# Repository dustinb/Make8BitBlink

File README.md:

# Make 8 Bit Blink

This is a program loader for [Ben Eater's 8 bit computer](https://eater.net/8bit/).  This is a work in progress.

# BOM

| Item                   | Link                   |
|------------------------|------------------------|
| ESP32                  | https://a.co/d/88cG9Z5 |
| 74HC595 Shift Register | https://a.co/d/fSzBLRR |
| PN2222 Transistors     | https://a.co/d/9t9HXHG |
| 40pin Socket Headers   | https://a.co/d/aSeVX48 |
| 22awg Hookup Wire      | https://a.co/d/aD9MhwA |

# Overview

The ESP32 polls the api (`/run` endpoint) for programs periodically.  If a program is in a queue the loader hatls the computer and loads the program.

# API

The api can by running `docker compose up` in the api directory.

Programs are queued in the order they are received.  A program can be queued by POSTing to the `/program` endpoint with the following JSON structure.

```json
{
    "clockSpeed": 100,
    "time": 20,
    "name": "42",
    "memory": [
        {
            "address": 14,
            "value": 28
        },
        {
            "address": 15,
            "value": 14
        }
    ],
    "instructions": [
        {
            "name": "LDA",
            "argument": 14
        },
        {
            "name": "ADD",
            "argument": 15
        },
        {
            "name": "OUT",
            "argument": 0
        },
        {
            "name": "HLT",
            "argument": 0
        }
    ]
}
```

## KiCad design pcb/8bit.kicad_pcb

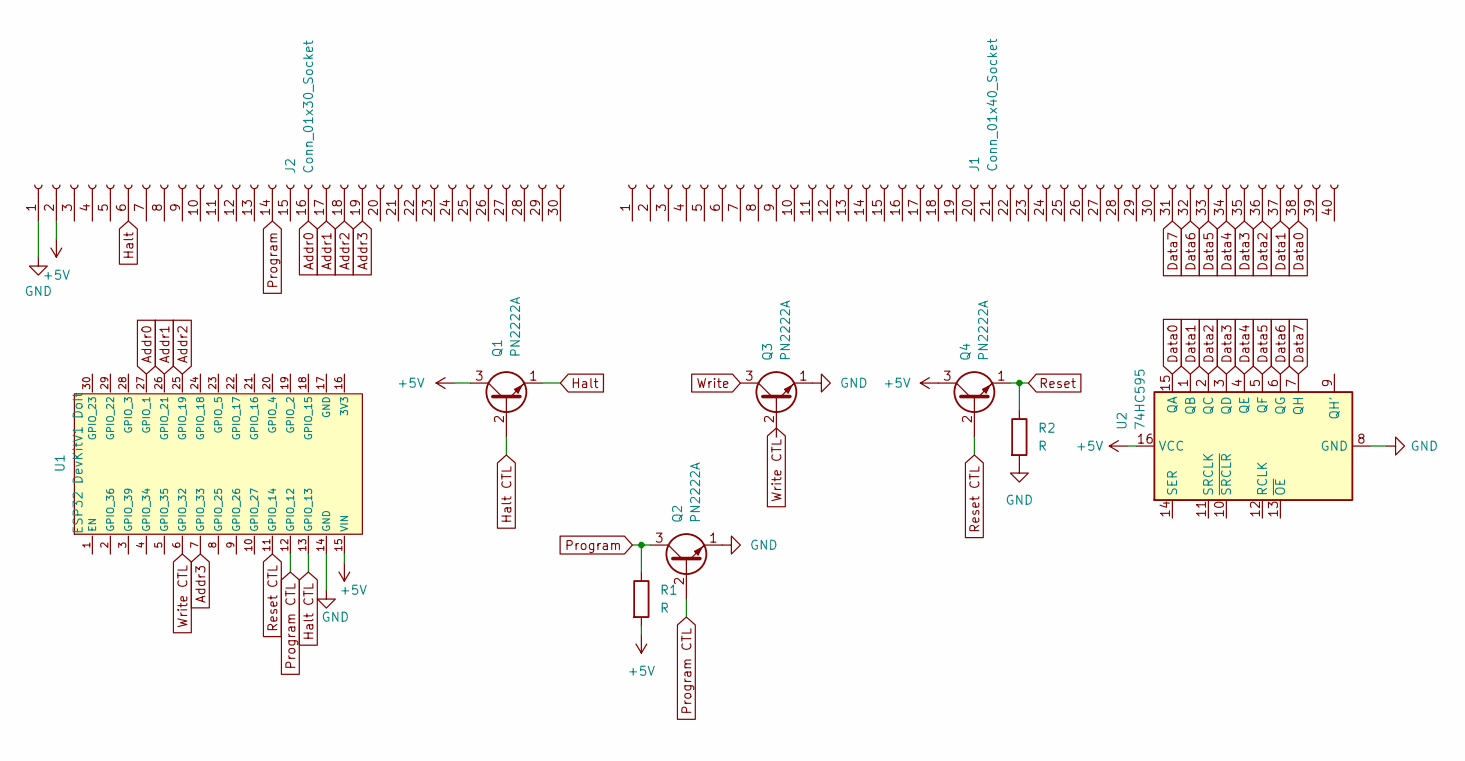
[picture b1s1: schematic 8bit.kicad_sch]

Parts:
J1: Conn_01x40_Socket; PinSocket_1x40_P2.54mm_Vertical
J2: Conn_01x30_Socket; PinSocket_1x30_P2.54mm_Vertical
Q1, Q2, Q3, Q4: PN2222A; TO-92_Inline
R1, R2: R; R_Axial_DIN0207_L6.3mm_D2.5mm_P10.16mm_Horizontal
U1: ESP32 DevKitV1 DoIt
U2: 74HC595; DIP-16_W7.62mm

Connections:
+5V: J2.2, Q1.3 (C), Q4.3 (C), R1.2, U1.15 (VIN), U2.16 (VCC)
Addr0: J2.16, U1.27 (GPIO_1)
Addr1: J2.17, U1.26 (GPIO_21)
Addr2: J2.18, U1.25 (GPIO_19)
Addr3: J2.19, U1.7 (GPIO_33)
Data0: J1.38, U2.15 (QA)
Data1: J1.37, U2.1 (QB)
Data2: J1.36, U2.2 (QC)
Data3: J1.35, U2.3 (QD)
Data4: J1.34, U2.4 (QE)
Data5: J1.33, U2.5 (QF)
Data6: J1.32, U2.6 (QG)
Data7: J1.31, U2.7 (QH)
GND: J2.1, Q2.1 (E), Q3.1 (E), R2.2, U1.14 (GND), U2.8 (GND)
Halt: J2.6, Q1.1 (E)
Halt CTL: Q1.2 (B), U1.13 (GPIO_13)
Program: J2.14, Q2.3 (C), R1.1
Program CTL: Q2.2 (B), U1.12 (GPIO_12)
Reset: Q4.1 (E), R2.1
Reset CTL: Q4.2 (B), U1.11 (GPIO_14)
Write: Q3.3 (C)
Write CTL: U1.6 (GPIO_32)

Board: 2 copper layers, 10 parts (0 on the bottom side), 20 nets, no tracks yet.

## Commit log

2023-11-19 Init 8bit loader
2023-11-19 Correct redis host
2023-11-19 Update BOM
